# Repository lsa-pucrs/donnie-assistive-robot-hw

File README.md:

# Donnie's PCB

This repository has all files related to Donnie's hardware (PCB design, schematics, eletrical diagrams, gerber files, BOM files). Donnie has two daugther boards (or 'shields'). One for the Arduino Mega (see ard-shield dir) and the other for the Raspberry Pi (see rasp-shield dir). 

The following image shows Donnie's brain and its electronics.  

## Manufacturing the boards

### Send the Gerber for manufacturing

If you just want to manufacture these boards as they are, we recommend the following steps:

 1. Send the Gerber ZIP files ([ard-shield](ard-shield/gerbers/ard_shield-160322-gerbers.zip) and [rasp-shield](rasp-shield/gerber_files/rasp_shield-gerber_files-160118.zip)) to manufacture to Seeedstudio. You should use the following tutorial [Fusion PCB Order Submission Guidelines](http://support.seeedstudio.com/knowledgebase/articles/422482-fusion-pcb-order-submission-guidelines)

### Assembly

 After you receive the PCBs, then follow these steps to assemble the boards:

 1. First of all, separe and buy the components indicated in BOM file ([ard-shield](ard-shield/BOM.txt) and [rasp-shield](rasp-shield/BOM.txt));
 2. Print the PDF schemmatic and BOM file;
 3. Place and weld the componnects in the PCB with the BOM's indicated PART.

## Change the PCB Design

If you want to change the PCB design, we recommend to use Eagle version XYZ.

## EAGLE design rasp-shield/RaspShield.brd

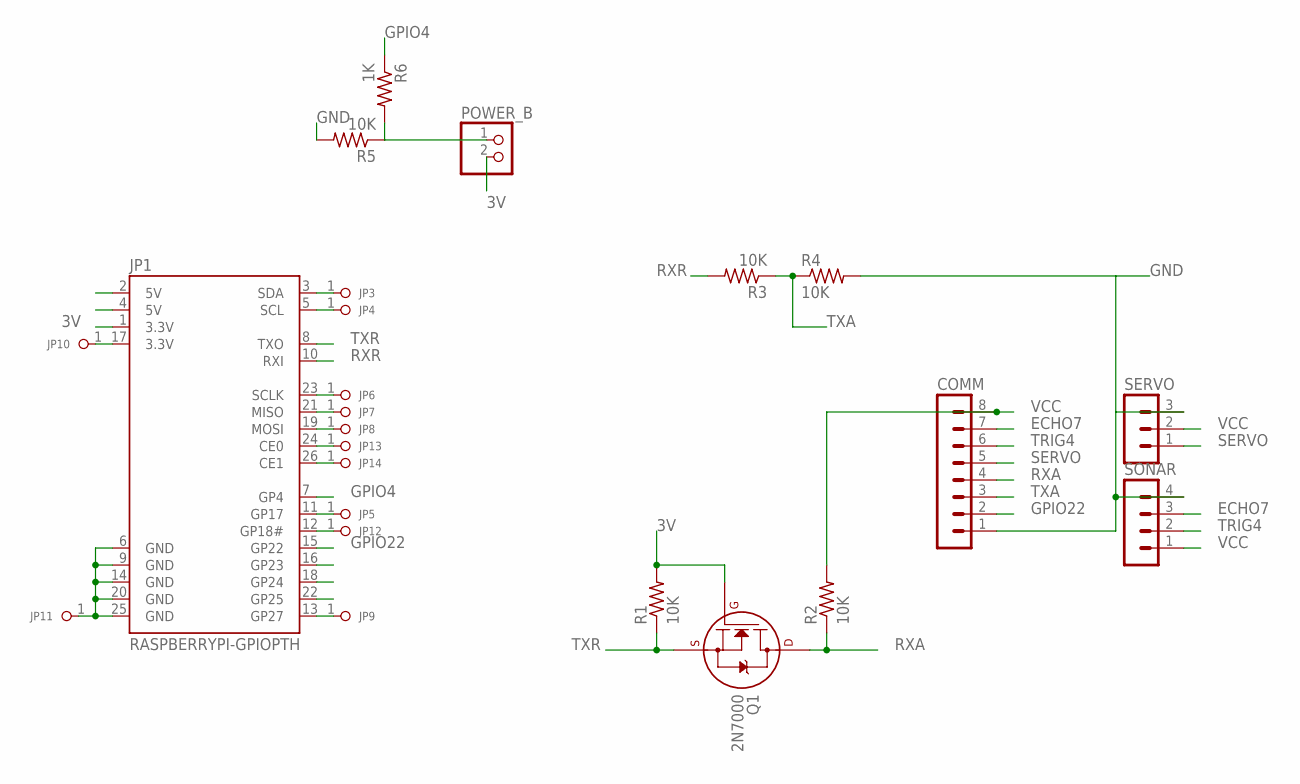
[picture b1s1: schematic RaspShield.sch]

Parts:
COMM: MA08-1
JP1: RASPBERRYPI-GPIOPTH; 2X13-SHROUDED
JP3, JP4, JP5, JP6, JP7, JP8, JP9, JP10, JP11, JP12, JP13, JP14: PINHD-1X1; 1X01
POWER_B: PINHD-1X2; 1X02
Q1: 2N7000; TO-92
R1, R2, R3, R4, R5: 10K; 0207/7
R6: 1K; 0207/7
SERVO: MA03-1
SONAR: MA04-1

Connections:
3V: JP1.1 (3.3V), POWER_B.2, Q1.2 (G), R1.2
ECHO7: COMM.7, SONAR.3
GND: COMM.1, R4.2, R5.2, SERVO.3, SONAR.4
GP2: JP1.3 (SDA), JP3.1
GP3: JP1.5 (SCL), JP4.1
GP7: JP1.26 (CE1), JP14.1
GP8: JP1.24 (CE0), JP13.1
GP9: JP1.21 (MISO), JP7.1
GP10: JP1.19 (MOSI), JP8.1
GP11: JP1.23 (SCLK), JP6.1
GP17: JP1.11 (GP17), JP5.1
GP18: JP1.12 (GP18#), JP12.1
GP23: JP1.16 (GP23)
GP24: JP1.18 (GP24)
GP25: JP1.22 (GP25)
GP27: JP1.13 (GP27), JP9.1
GPIO4: JP1.7 (GP4), R6.1
GPIO22: COMM.2, JP1.15 (GP22)
unnamed: JP1.17 (3.3V), JP10.1
unnamed: POWER_B.1, R5.1, R6.2
unnamed: JP1.6 (GND), JP1.9 (GND), JP1.14 (GND), JP1.20 (GND), JP1.25 (GND), JP11.1
RXA: COMM.4, Q1.3 (D), R2.1
RXR: JP1.10 (RXI), R3.2
SERVO: COMM.5, SERVO.1
TRIG4: COMM.6, SONAR.2
TXA: COMM.3, R3.1, R4.1
TXR: JP1.8 (TXO), Q1.1 (S), R1.1
VCC: COMM.8, R2.2, SERVO.2, SONAR.1

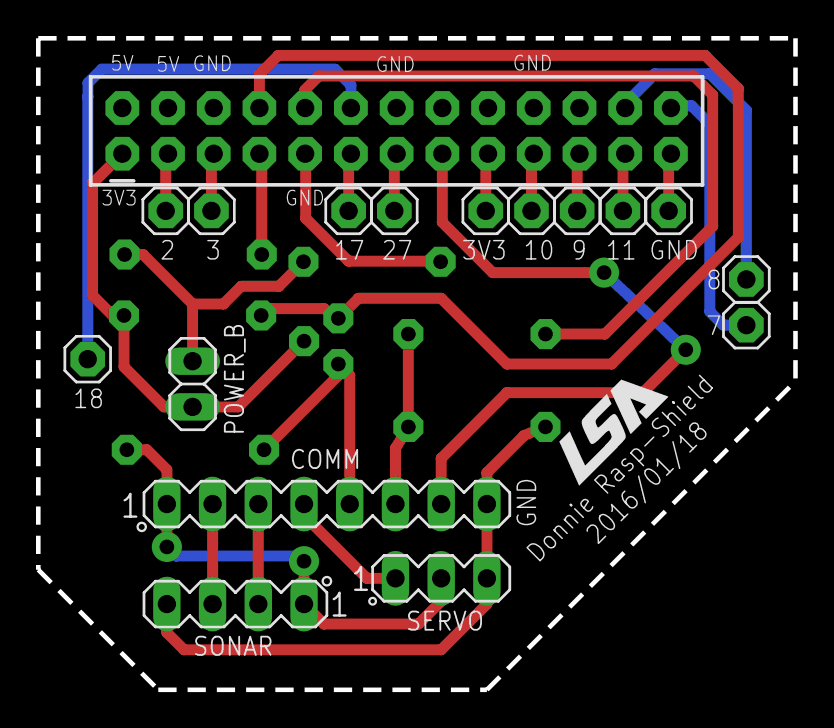
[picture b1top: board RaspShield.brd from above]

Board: 2 copper layers, 42.1 x 36.2 mm, 24 parts (1 on the bottom side), 25 nets.

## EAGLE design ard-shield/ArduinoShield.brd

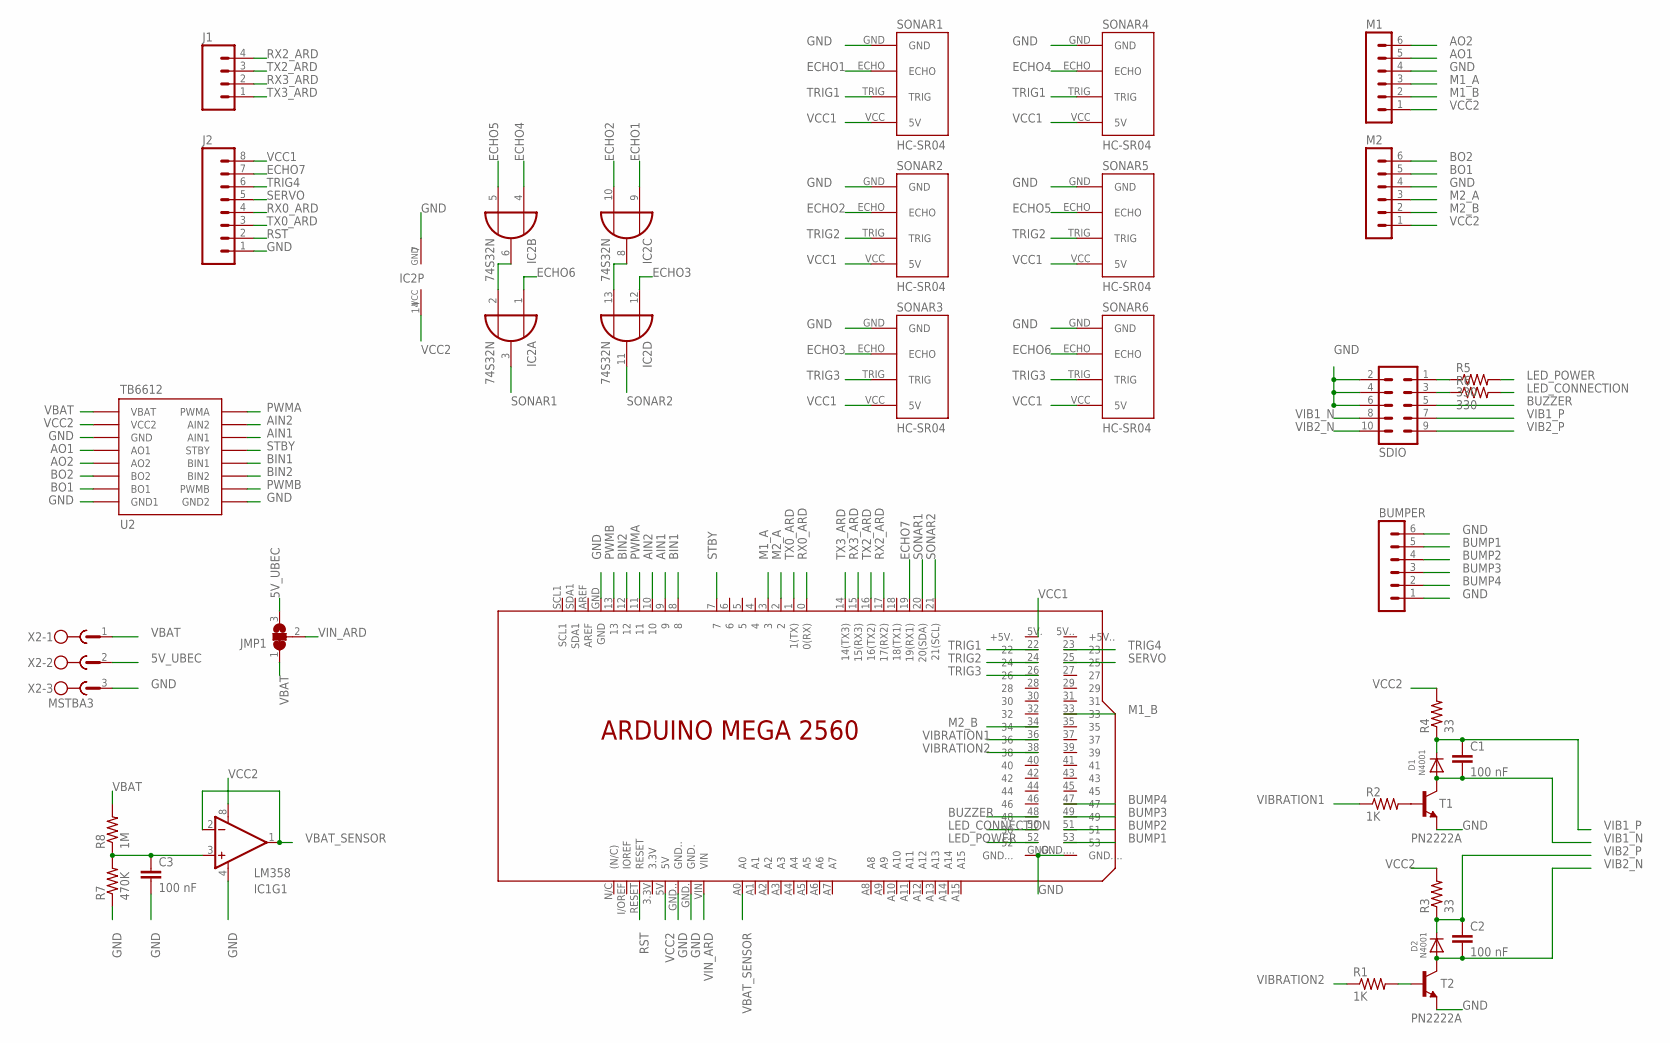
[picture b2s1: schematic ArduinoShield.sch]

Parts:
BUMPER: MA06-1
C1, C2, C3: 100 nF; C5B2.5
D1, D2: N4001; DO-1N4148
IC1: LM358; DIP08
IC2: 74S32N; DIL14
J1: M04PTH; 1X04
J2: M08SILK_FEMALE_PTH; 1X08
JMP1: SJ2W; SJ_2
M1, M2: MA06-1
PCB1: ARDUINO_MEGA2560
R1, R2: 1K; 0207/2V
R3, R4: 33; 0207/2V
R5, R6: 330; 0207/2V
R7: 470K; 0207/2V
R8: 1M; 0207/2V
SDIO: MA05-2
SONAR1, SONAR2, SONAR3, SONAR4, SONAR5, SONAR6: HC-SR04; HC-SR04_FOOTPRINT
T1, T2: PN2222A; TO92-EBC-OVAL
U2: TB6612
X2: MSTBA3

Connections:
5V_UBEC: JMP1.3, X2.2
AIN1: PCB1.9, U2.P$14 (AIN1)
AIN2: PCB1.10, U2.P$15 (AIN2)
AO1: M1.5, U2.P$4 (AO1)
AO2: M1.6, U2.P$5 (AO2)
BIN1: PCB1.8, U2.P$12 (BIN1)
BIN2: PCB1.12, U2.P$11 (BIN2)
BO1: M2.5, U2.P$7 (BO1)
BO2: M2.6, U2.P$6 (BO2)
BUMP1: BUMPER.5, PCB1.53
BUMP2: BUMPER.4, PCB1.51
BUMP3: BUMPER.3, PCB1.49
BUMP4: BUMPER.2, PCB1.47
BUZZER: PCB1.48, SDIO.5
ECHO1: IC2.9 (I0), SONAR1.ECHO
ECHO2: IC2.10 (I1), SONAR2.ECHO
ECHO3: IC2.12 (I0), SONAR3.ECHO
ECHO4: IC2.4 (I0), SONAR4.ECHO
ECHO5: IC2.5 (I1), SONAR5.ECHO
ECHO6: IC2.1 (I0), SONAR6.ECHO
ECHO7: J2.7, PCB1.19 (19(RX1))
GND: BUMPER.1, BUMPER.6, C3.2, IC1.4 (V-), IC2.7 (GND), J2.1, M1.4, M2.4, PCB1.GND, PCB1.GND., PCB1.GND.., PCB1.GND..., PCB1.GND...., R7.1, SDIO.2, SDIO.4, SDIO.6, SONAR1.GND, SONAR2.GND, SONAR3.GND, SONAR4.GND, SONAR5.GND, SONAR6.GND, T1.E, T2.E, U2.P$3 (GND), U2.P$8 (GND1), U2.P$9 (GND2), X2.3
LED_CONNECTION: PCB1.50, R6.2
LED_POWER: PCB1.52, R5.2
M1_A: M1.3, PCB1.3
M1_B: M1.2, PCB1.33
M2_A: M2.3, PCB1.2
M2_B: M2.2, PCB1.34
unnamed: R2.2, T1.B
unnamed: IC2.2 (I1), IC2.6 (O)
unnamed: R1.2, T2.B
unnamed: IC2.8 (O), IC2.13 (I1)
unnamed: R5.1, SDIO.1
unnamed: R6.1, SDIO.3
unnamed: C3.1, IC1.3 (+IN), R7.2, R8.1
PWMA: PCB1.11, U2.P$16 (PWMA)
PWMB: PCB1.13, U2.P$10 (PWMB)
RST: J2.2, PCB1.RESET
RX0_ARD: J2.4, PCB1.0 (0(RX))
RX2_ARD: J1.4, PCB1.17 (17(RX2))
RX3_ARD: J1.2, PCB1.15 (15(RX3))
SERVO: J2.5, PCB1.25
SONAR1: IC2.3 (O), PCB1.20 (20(SDA))
SONAR2: IC2.11 (O), PCB1.21 (21(SCL))
STBY: PCB1.7, U2.P$13 (STBY)
TRIG1: PCB1.22, SONAR1.TRIG, SONAR4.TRIG
TRIG2: PCB1.24, SONAR2.TRIG, SONAR5.TRIG
TRIG3: PCB1.26, SONAR3.TRIG, SONAR6.TRIG
TRIG4: J2.6, PCB1.23
TX0_ARD: J2.3, PCB1.1 (1(TX))
TX2_ARD: J1.3, PCB1.16 (16(TX2))
TX3_ARD: J1.1, PCB1.14 (14(TX3))
VBAT: JMP1.1, R8.2, U2.P$1 (VBAT), X2.1
VBAT_SENSOR: IC1.1 (OUT), IC1.2 (-IN), PCB1.A0
VCC1: J2.8, PCB1.5V. (+5V.), SONAR1.VCC (5V), SONAR2.VCC (5V), SONAR3.VCC (5V), SONAR4.VCC (5V), SONAR5.VCC (5V), SONAR6.VCC (5V)
VCC2: IC1.8 (V+), IC2.14 (VCC), M1.1, M2.1, PCB1.5V, R3.2, R4.2, U2.P$2 (VCC2)
VIB1_N: C1.2, D1.A, SDIO.8, T1.C
VIB1_P: C1.1, D1.C, R4.1, SDIO.7
VIB2_N: C2.2, D2.A, SDIO.10, T2.C
VIB2_P: C2.1, D2.C, R3.1, SDIO.9
VIBRATION1: PCB1.36, R2.1
VIBRATION2: PCB1.38, R1.1
VIN_ARD: JMP1.2, PCB1.VIN

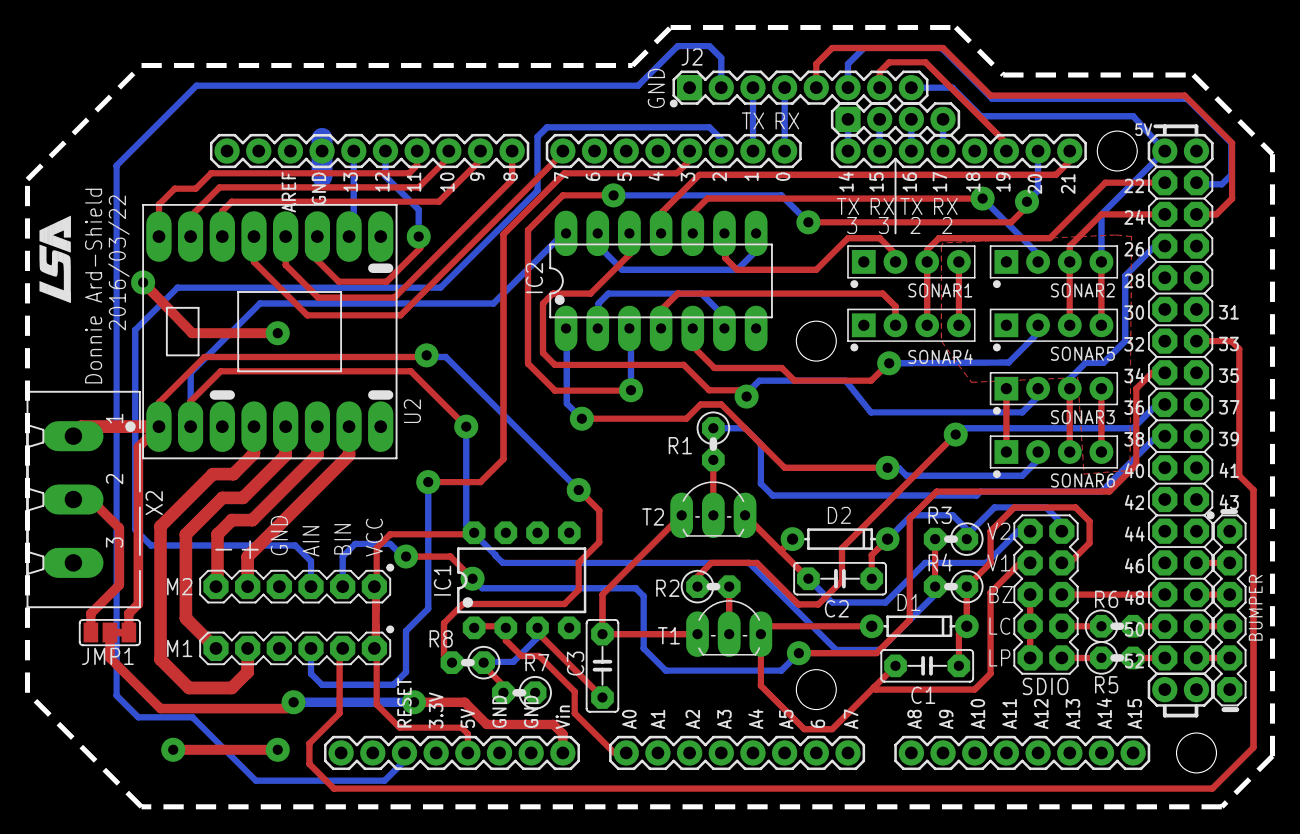
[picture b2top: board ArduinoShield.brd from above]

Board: 2 copper layers, 99.8 x 62.5 mm, 33 parts (0 on the bottom side), 63 nets.

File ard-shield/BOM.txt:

Qty Value            Device             Package           Parts

2                    MALE HEADER        1X04              J1, J2-BELOW
6                    MALE HEADER        1X08              J2, 5XARDUINO-MEGA-SHIELD-CONNECTORS
1                    MALE HEADER        1X10              ARDUINO-MEGA-SHIELD-CONNECTORS
1                    MALE HEADER        2X18              ARDUINO-MEGA-SHIELD-CONNECTORS
1                    MALE HEADER        2X05              SDIO
3                    MALE HEADER        1X06              BUMPER, M1, M2
2                    FEMALE HEADER      1X08              U2-HEADER
6                    MALE HEADER        1X04              SONAR1, SONAR2, SONAR3, SONAR4, SONAR5, SONAR6
1                    IC SOCKET          14 PIN            IC2-SOCKET
1                    IC SOCKET          8 PIN             IC1-SOCKET
1                    KRE CONNECTOR      1X3 5MM           X2
3   100 nF           CAPACITOR          POLYESTER 100V    C1, C2, C3
2   1K               RESISTOR           PTH 1/4W          R1, R2
1   1M               RESISTOR           PTH 1/4W          R8
2   33               RESISTOR           PTH 1/4W          R3, R4
2   330              RESISTOR           PTH 1/4W          R5, R6
1   470K             RESISTOR           PTH 1/4W          R7
2   1N4001           DIODO              DO-204AL          D1, D2
2   2N2222A          NPN TRANSISTOR     O92               T1, T2
1   74S32N           OR GATE            DIL14             IC2
1   LM358            OP AMP             DIP08             IC1
1   TB6612           MOTOR DRIVER       MODULE            U2

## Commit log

2016-07-13 added files of first boards manufactured
2016-07-13 Added the BOMs files and contruction resume
2016-08-18 updating readme.md
    improved instructions to build the PCBs
2017-04-06 add simplified schematics image
2017-04-06 including fritzing file in the readme
2019-04-30 including vib-belt schematics done by Igor
2019-04-30 additional files fom vib_belt
2019-05-02 added BOM file
2019-05-09 Including vib-belt schematics for use with Nano

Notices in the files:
parts and their libraries:
SparkFun-AnalogIC: Licensing:Creative Commons ShareAlike 4.0 International - https://creativecommons.org/licenses/by-sa/4.0
